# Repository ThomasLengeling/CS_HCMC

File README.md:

# CS_HCMC
Interaction Application for CS Vietnam

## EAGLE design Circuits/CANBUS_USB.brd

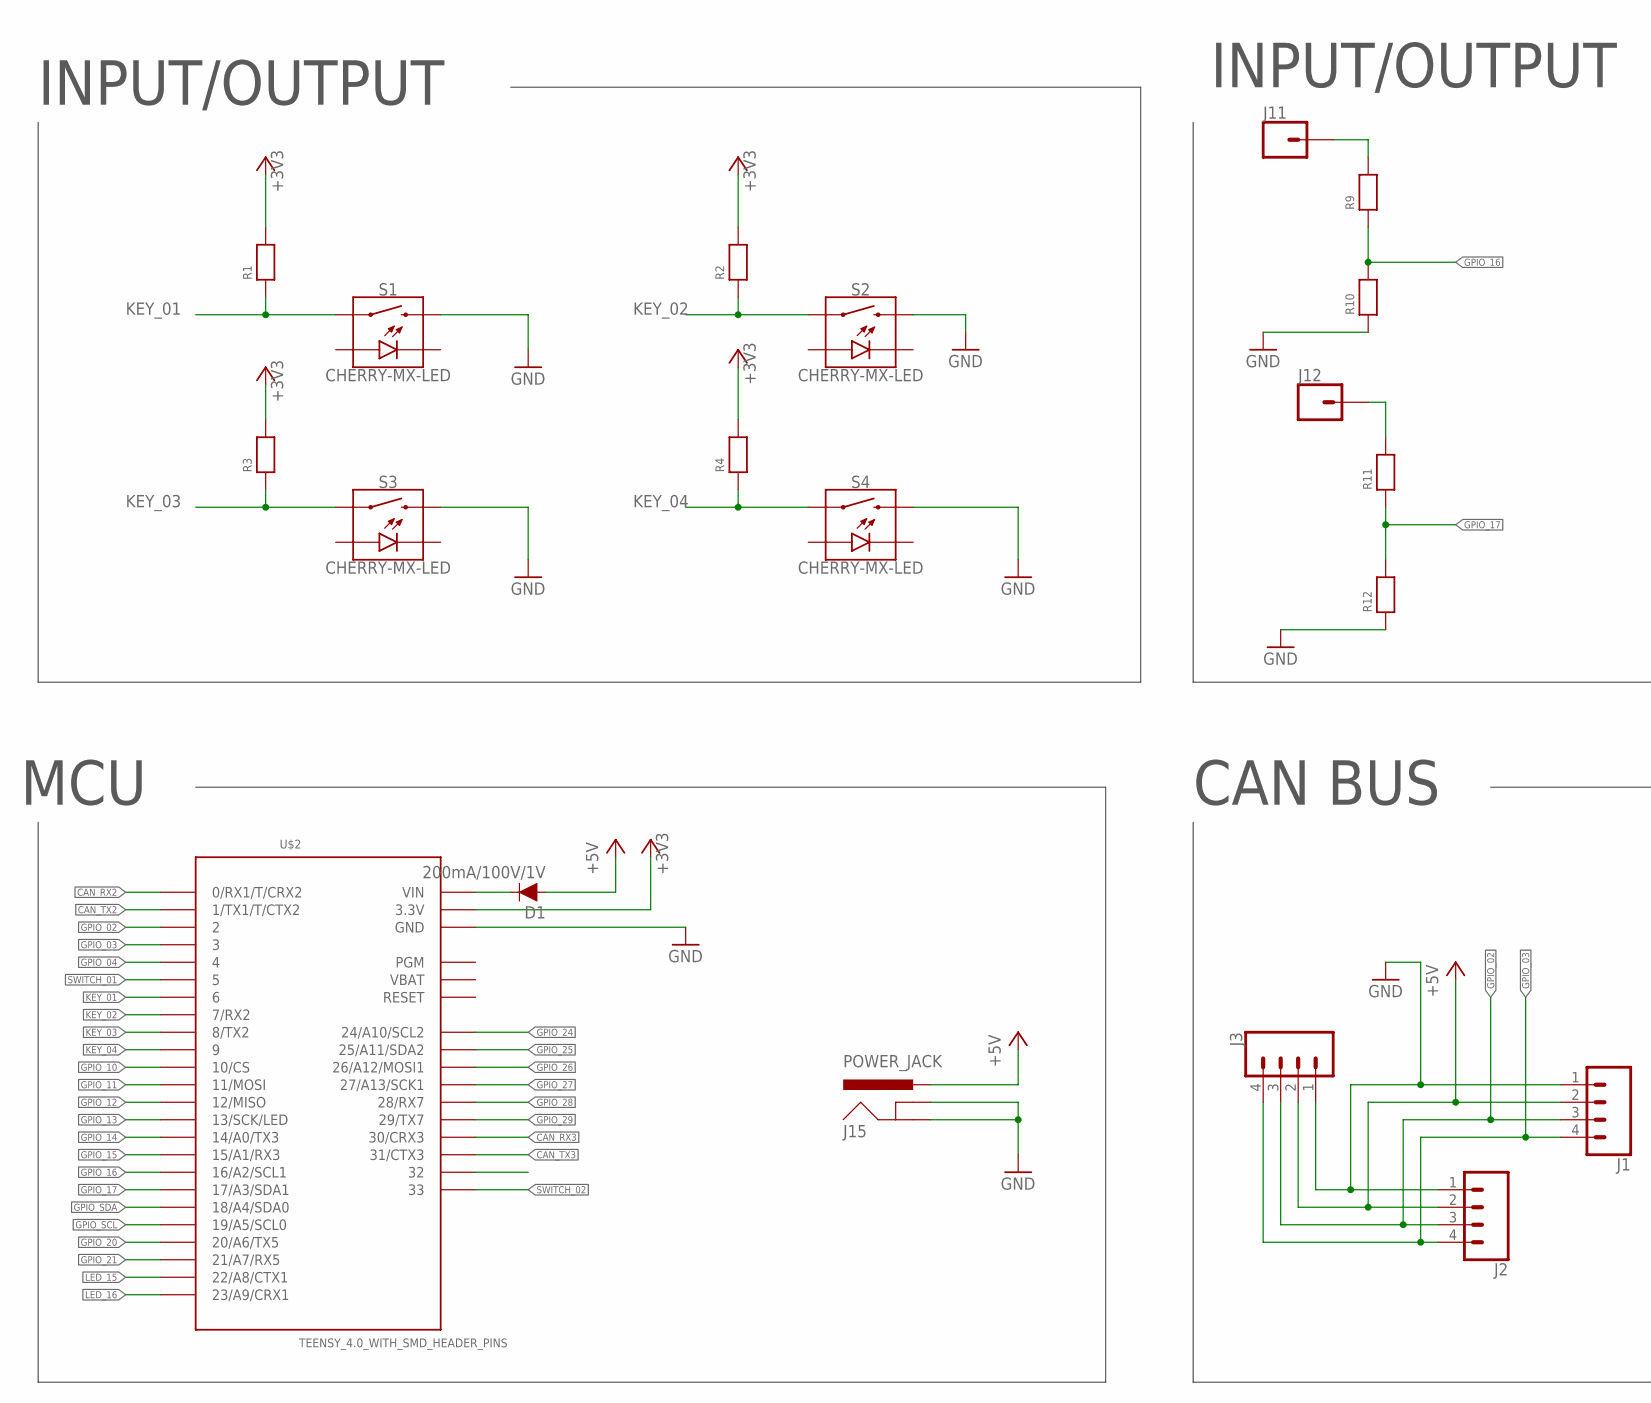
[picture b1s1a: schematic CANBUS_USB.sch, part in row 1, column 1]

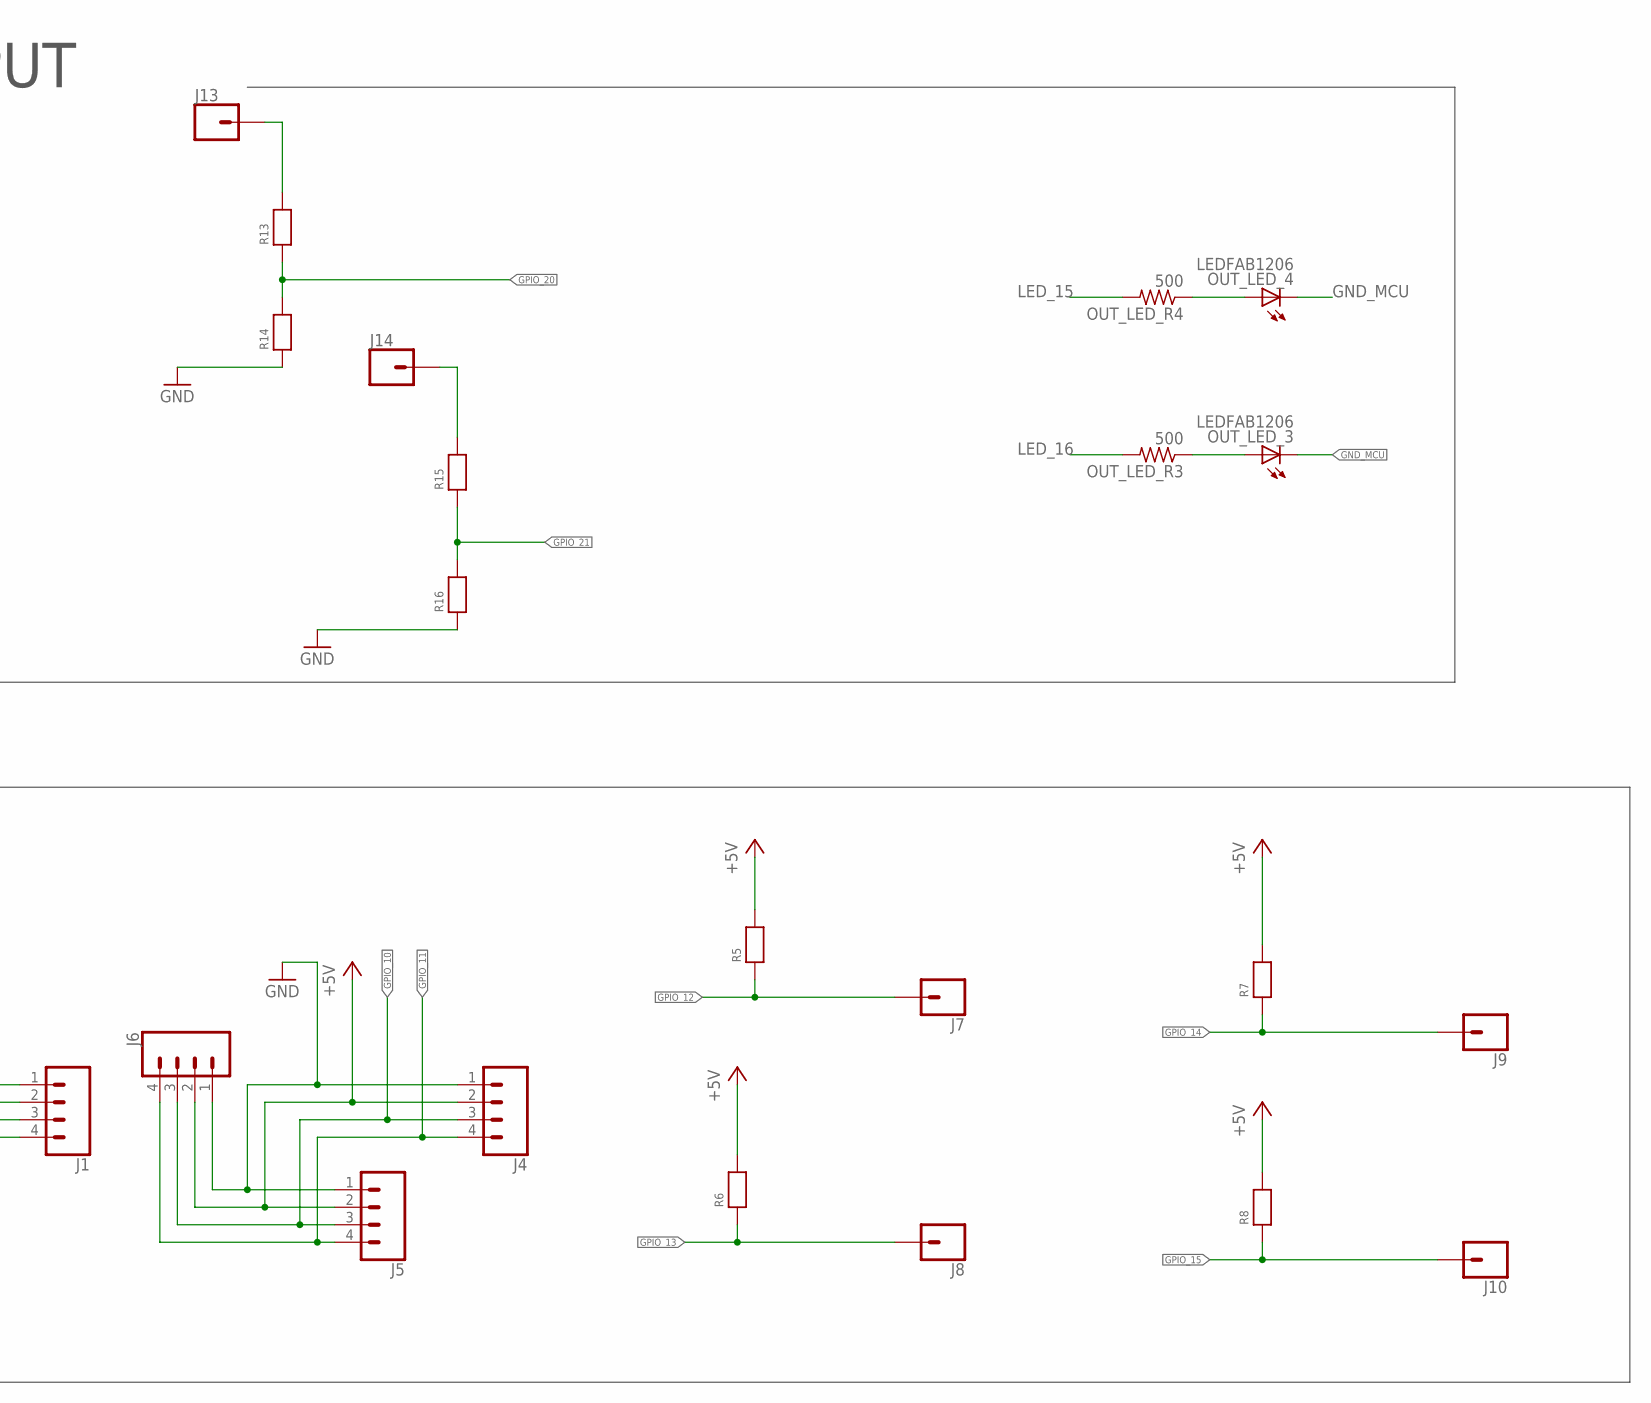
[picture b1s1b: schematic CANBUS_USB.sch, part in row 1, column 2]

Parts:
D1: 200mA/100V/1V; DIODE-1N4148
J1, J2, J3, J4, J5, J6: CONN_04; 1X04
J7, J8, J9, J10, J11, J12, J13, J14: CONN_01; 1X01
J15: POWER_JACK; POWER_JACK_PTH
OUT_LED_3, OUT_LED_4: LEDFAB1206; LED1206FAB
OUT_LED_R3, OUT_LED_R4: 500; R1206FAB
R1, R2, R3, R4, R5, R6, R7, R8, R9, R10, R11, R12, R13, R14, R15, R16: RESISTOR1206; 1206
S1, S2, S3, S4: CHERRY-MX-LED
U$2: TEENSY_4.0_WITH_SMD_HEADER_PINS

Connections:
+3V3: R1.2, R2.2, R3.2, R4.2, U$2.3.3V, U$2.3.3V1 (3.3V)
+5V: D1.A, J1.2, J2.2, J3.2, J4.2, J5.2, J6.2, J15.PWR, R5.2, R6.2, R7.2, R8.2
CAN_RX2: U$2.0 (0/RX1/T/CRX2)
CAN_RX3: U$2.30 (30/CRX3)
CAN_TX2: U$2.1 (1/TX1/T/CTX2)
CAN_TX3: U$2.31 (31/CTX3)
GND: J1.1, J2.1, J3.1, J4.1, J5.1, J6.1, J15.GND, J15.GNDBREAK, R10.1, R12.1, R14.1, R16.1, S1.S2, S2.S2, S3.S2, S4.S2, U$2.GND, U$2.GND1 (GND), U$2.GND2 (GND)
GND_MCU: OUT_LED_3.2 (C), OUT_LED_4.2 (C)
GPIO_02: J1.3, J2.3, J3.3, U$2.2
GPIO_03: J1.4, J2.4, J3.4, U$2.3
GPIO_04: U$2.4
GPIO_10: J4.3, J5.3, J6.3, U$2.10 (10/CS)
GPIO_11: J4.4, J5.4, J6.4, U$2.11 (11/MOSI)
GPIO_12: J7.1, R5.1, U$2.12 (12/MISO)
GPIO_13: J8.1, R6.1, U$2.13 (13/SCK/LED)
GPIO_14: J9.1, R7.1, U$2.14/A0 (14/A0/TX3)
GPIO_15: J10.1, R8.1, U$2.15/A1 (15/A1/RX3)
GPIO_16: R9.1, R10.2, U$2.16/A2 (16/A2/SCL1)
GPIO_17: R11.1, R12.2, U$2.17/A3 (17/A3/SDA1)
GPIO_20: R13.1, R14.2, U$2.20/A6 (20/A6/TX5)
GPIO_21: R15.1, R16.2, U$2.21/A7 (21/A7/RX5)
GPIO_24: U$2.24 (24/A10/SCL2)
GPIO_25: U$2.25 (25/A11/SDA2)
GPIO_26: U$2.26 (26/A12/MOSI1)
GPIO_27: U$2.27 (27/A13/SCK1)
GPIO_28: U$2.28 (28/RX7)
GPIO_29: U$2.29 (29/TX7)
GPIO_SCL: U$2.19/A5 (19/A5/SCL0)
GPIO_SDA: U$2.18/A4 (18/A4/SDA0)
KEY_01: R1.1, S1.S1, U$2.6
KEY_02: R2.1, S2.S1, U$2.7 (7/RX2)
KEY_03: R3.1, S3.S1, U$2.8 (8/TX2)
KEY_04: R4.1, S4.S1, U$2.9
LED_15: OUT_LED_R4.2, U$2.22/A8 (22/A8/CTX1)
LED_16: OUT_LED_R3.2, U$2.23/A9 (23/A9/CRX1)
unnamed: J11.1, R9.2
unnamed: J13.1, R13.2
unnamed: J12.1, R11.2
unnamed: J14.1, R15.2
unnamed: OUT_LED_3.1 (A), OUT_LED_R3.1
unnamed: OUT_LED_4.1 (A), OUT_LED_R4.1
unnamed: D1.C, U$2.VIN
SWITCH_01: U$2.5
SWITCH_02: U$2.33
VBAT: U$2.VBAT

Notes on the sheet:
MCU
INPUT/OUTPUT
CAN BUS

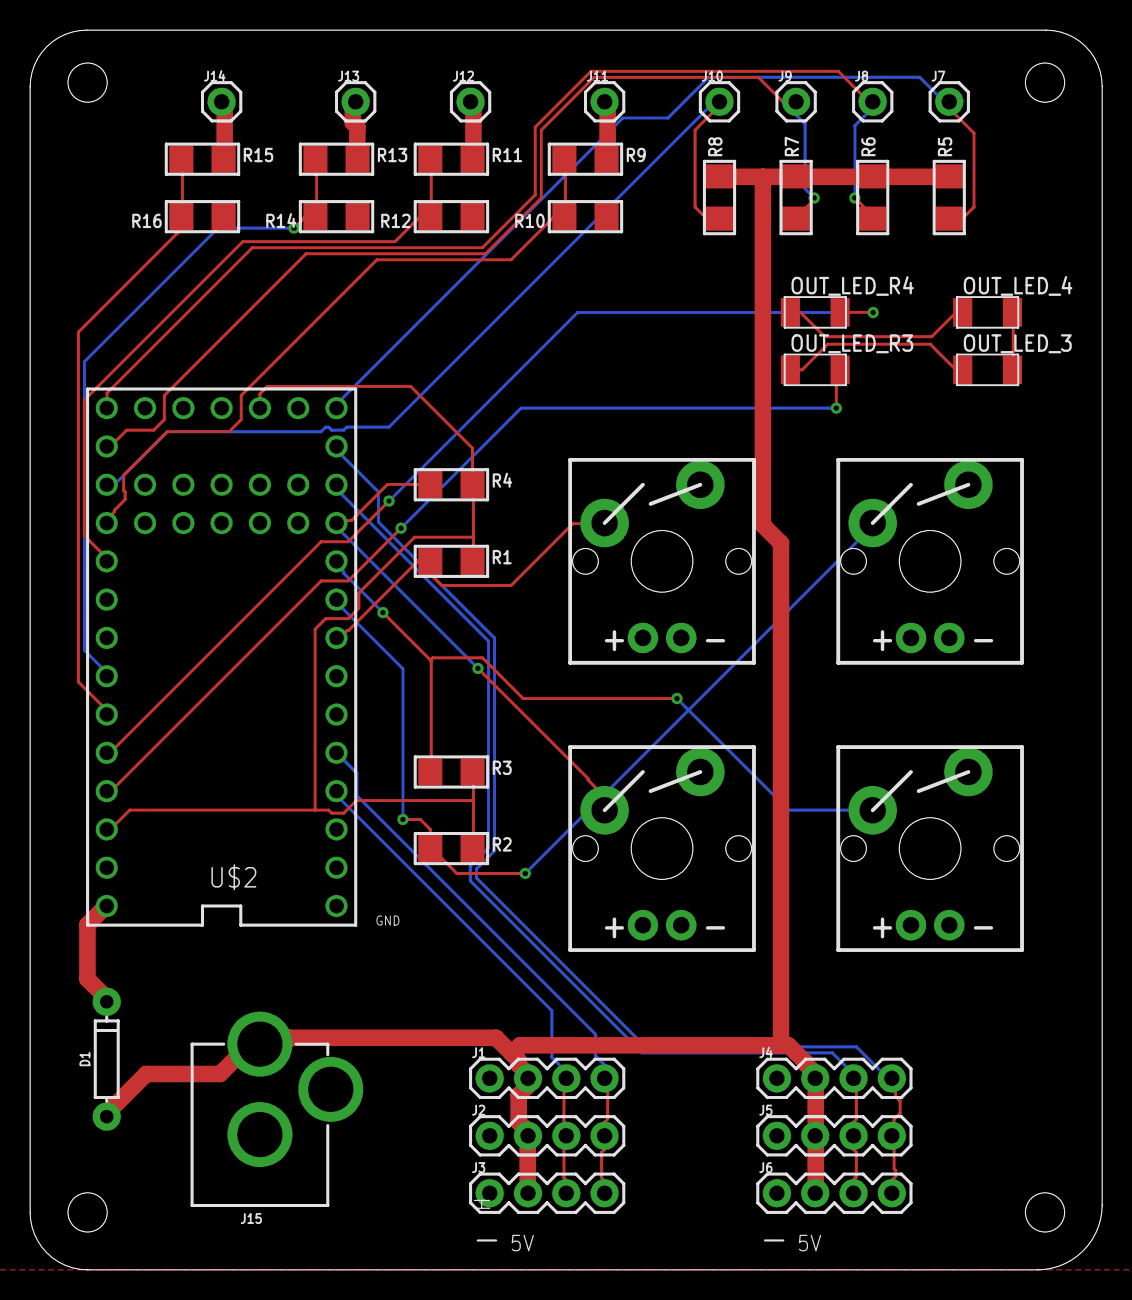
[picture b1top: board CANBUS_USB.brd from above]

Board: 2 copper layers, 71.1 x 82.2 mm, 41 parts (0 on the bottom side), 29 nets.

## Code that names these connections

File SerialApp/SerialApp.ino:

#include <Bounce.h>

#define KEY_01 6
#define KEY_02 7
#define KEY_03 8
#define KEY_04 9

#define LED_01 22
#define LED_02 23


// Instantiate a Bounce object with a 100 millisecond debounce time
#define TIME_DEBOUNCE 20


const int NUM_KEYS = 4;
uint8_t key_pins[] = {KEY_01, KEY_02, KEY_03, KEY_04};

byte serial_buffer[] = {0, 0, 0, 0};
byte serial_bufferP[] =  {0, 0, 0, 0};

Bounce * bouncer[NUM_KEYS];

void setup() {
  // put your setup code here, to run once:

  Serial.begin(9600);

  pinMode(KEY_01, INPUT);
  pinMode(KEY_02, INPUT);
  pinMode(KEY_03, INPUT);
  pinMode(KEY_04, INPUT);

  pinMode(LED_01, OUTPUT);
  pinMode(LED_02, OUTPUT);
  pinMode(13, OUTPUT );


  digitalWrite(LED_01, HIGH);
  digitalWrite(LED_02, HIGH);
  digitalWrite(13, HIGH );
  delay(500);

  digitalWrite(LED_01, LOW);
  digitalWrite(LED_02, LOW);
  digitalWrite(13, LOW );


  for (int i = 0; i < NUM_KEYS; i++) {
    bouncer[i] = new Bounce(key_pins[i], TIME_DEBOUNCE);
  }
}

void loop() {
  
  for (int i = 0; i < NUM_KEYS; i++) {
    bouncer[i]->update ( );
    serial_bufferP[i] = serial_buffer[i];
    int keyPressed =  bouncer[i]->read();
    if (keyPressed == HIGH) {
      serial_buffer[i] = 1;
      digitalWrite(LED_02, LOW );
    } else {
      serial_buffer[i] = 0;
      digitalWrite(LED_02, HIGH );
    }

  }

  //Check if therw was a change in the state of the button
  boolean foundChange = false;
  for (int i = 0; i < NUM_KEYS; i++) {
    if ( serial_bufferP[i]  != serial_buffer[i]) {
      foundChange = true;
      digitalWrite(13, HIGH );   
      break;
    }else{
      digitalWrite(13, LOW );
    }
  }

  //send serial
  if (foundChange) {
    Serial.write(serial_buffer, 4);
  }






}

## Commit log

2021-05-10 first project of
2021-05-10 working communication with arduino and webapp
2021-05-10 working different msg to client
2021-05-27 circuit

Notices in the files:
parts and their libraries:
microbuilder: This work is placed in the public domain, and may be freely used for commercial and non-commercial work with the following conditions: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
SparkFun-Connectors: Licensing: Creative Commons ShareAlike 4.0 International - https://creativecommons.org/licenses/by-sa/4.0
